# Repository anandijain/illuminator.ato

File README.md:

# illuminator
a device to capture timelapses of fluorescent petri dishes

[Onshape CAD](https://cad.onshape.com/documents/1effa1616a317fb48e7ffbf3/w/ae2fe78dc753e01a133967d8/e/a3ef25508ab919a74d42227d?renderMode=0&uiState=692bc1250b43d9fa593e8de2)

[YouTube](https://youtube.com/playlist?list=PL79kqjVnD2ENzYDWSiDm63MTBGJOrp2XY&si=uE8JB_jzI9ln5rCQ)

petri dish illuminator for timelapses 
the functionality basically has an 
* mcu turn on a bunch of lights
* light goes thru a diffuser
* hit the petri (excite the fluorescent protein)
* into a filter 
* imaged via timelapse on a DSLR 

there are two modes to use the device
Common to both modes is using a GPIO pin to turn on a mosfet that turns on an LED grid. 

## Raspberry Pi Pico 
the first is using a raspberry pi pico, and the second is using a full fledged Pi. 
However, we still need to tell the camera to take a photo while the lights are on. 
The pico accomplishes this by using a GPIO pin to drive an optocoupler, which connects to the [MC-DC2](https://www.dslrbodies.com/cameras/general-nikon-camera-info/nikon-mc-dc2-connector-pin.html) port. 
Basically the opto provides a short between the Tip and the Sleeve, triggering a photo to be taken.

## Raspberry Pi 
Unfortunately, this method requires providing power for the board and the Pi separately (two power cables). 
Basically, a USB cable is connects the Pi to Nikon's semi-proprietary UC-E6 "USB" port. 
Then we use `gphoto2` to trigger the camera and download it to the Pi.

the design is as follows, a 5V 5A (5A is excessive, you probably dont need more than 2-3A) wall wart plugs to a barrel jack

the barrel jack tip will go to VBus of the USB port and the 36 resistor-led pairs (all parallel)

the ground of the barrel goes to the gnd of the USB. 

The usb is an TYPE-A connector that is used solely for powering the Pico (DO NOT USE FOR A FULL PI, the USB 2.0 spec is limited at 1.5A but a Pi can draw 5A.)

## pinouts 
There is a TRS (i dont like JST) port used for connecting GPIO from Pi/Pico to the board.
The Tip of `trs_sig` is only used by the pico, and is for turning on the optocoupler
The Ring is used by both for turning on the FET (the LEDs)
The Sleeve is GND. 

Note: on the TRS breakout cable, white is tip (pico w pin GP16), red is ring (pico w pin GP17), black is sleeve (pico w pin 23 (GND))

A second TRS connector is used to connect the MC-DC2 connector from camera to the optocoupler. Unfortunately, it seems common that MC-DC2 uses a 2.5mm TRS, but I am just going to use an adapter so that I don't need to buy 2.5mm jacks that I'll never use. 

The path is 5v -> (R -> LED)* -> FET_DRAIN -> FET_SOURCE -> GND.

## camera 
* make sure no autofocus is on cuz that increases the time to shorting the MC-DC2 to an unknown amount of time

## lcd
* to get mc_dc2_test/lcd.py to work you need to copy [this](https://github.com/russhughes/st7789py_mpy/blob/master/lib/st7789py.py) to /lib/ with `mpremote`

remember to also copy the fonts 

the interface of the lcd is three buttons, two are for incrementing and decrementing the timelapse parameters the third is for advancing to the next parameter

todo ui:
- see if its possible to start timelapse when both + and - are hit simultaneously or something

TODO before order:

Done:
* fix mounting holes position
* cad enclosure and box 
* order the diffuser and lens
*silkscreen art 

## board images (no kicad schematic see main.ato)

## some BOM items
* [light diffuser](https://www.amazon.com/dp/B0818HYY8G)
* [hot plate for SMD soldering](https://www.amazon.com/dp/B082H12PPT)

### 8/28/25 

the general design will be relatively agnostic to the excitation wavelength, 
allowing multiple different proteins to be timelapsed 

TODO:
- resistor sizing for each string of LEDs
- can i PWM my N-mosfet that controls the leds? 

https://chatgpt.com/share/68b0b650-5c54-8009-a0fc-7b128db387fa

even though the excitation peak of [A. Victoria's GFP gene](https://www.fpbase.org/protein/avgfp/) is at 395 nm (UVA range), 
there is evidence that photobleaching occurs and can inhibit cell growth.

that, in addition to the eyes/skin risk of penetrating UV, we will use the weaker excitation peak of 
475 nm 

there are two primary routes to acheiving timelapses, 

the first is using a Pico and a port on the D7100 called MC-DC2 

the second is using a full RPi with gphoto2, this allows the collection of the photos onto the Pi

after extensive reading: the grid of LEDs will be 12 strings of 3 LEDs, powered by a 12V rail

maybe instead of a buck since it seems sparse to find preset 5V bucks at 3A (enought to power Pi)
and the ones that are adjustable seem annoying to implement

if we are going with the Pico, then its a bit easier since it's not going to need 5V 3A.

math

datasheet of led -> radiative flux (mW) -> photons/sec

concentration of GFP + QY + photons/sec -> number of emitted photons/sec

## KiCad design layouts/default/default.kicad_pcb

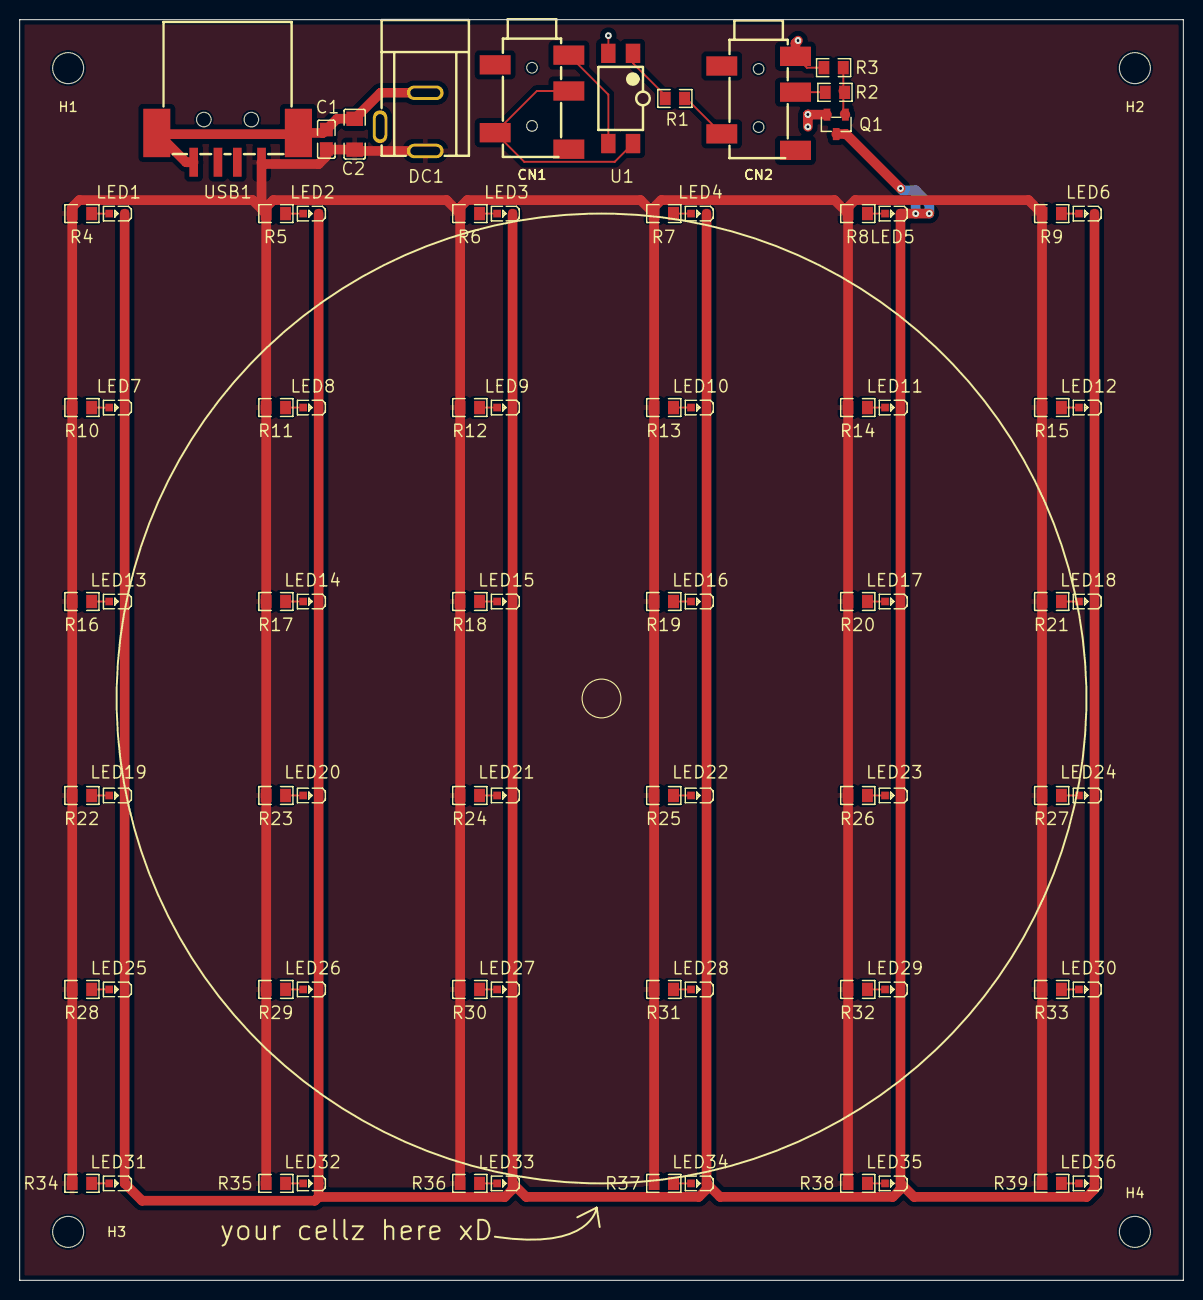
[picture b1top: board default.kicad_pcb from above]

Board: 2 copper layers, 120.0 x 130.0 mm, 87 parts (0 on the bottom side), 45 nets.

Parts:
C1: C0805
C2: C1206
CN1, CN2: AUDIO-SMD_PJ-327A5JJ
DC1: DC-IN-TH_DC-005-A200
H1, H2, H3, H4: MountingHole_3.2mm_M3
LED1, LED2, LED3, LED4, LED5, LED6, LED7, LED8, LED9, LED10, LED11, LED12, LED13, LED14, LED15, LED16, LED17, LED18, LED19, LED20, LED21, LED22, LED23, LED24, LED25, LED26, LED27, LED28, LED29, LED30, LED31, LED32, LED33, LED34, LED35, LED36: LED0603-RD_BLUE
Q1: SOT-23-3_L2.9-W1.3-P1.90-LS2.4-BR
R1, R2, R3, R4, R5, R6, R7, R8, R9, R10, R11, R12, R13, R14, R15, R16, R17, R18, R19, R20, R21, R22, R23, R24, R25, R26, R27, R28, R29, R30, R31, R32, R33, R34, R35, R36, R37, R38, R39: R0805
U1: SMD-4_L4.6-W6.5-P2.54-LS10.2-TL
USB1: USB-A-SMD_USB-234-BCW

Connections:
G: Q1.1, R2.2, R3.1
GND: C1.2, C2.2, CN2.1, DC1.2, Q1.2, R3.2, U1.2, USB1.4, USB1.5, USB1.6
K: LED1.1, LED2.1, LED3.1, LED4.1, LED5.1, LED6.1, LED7.1, LED8.1, LED9.1, LED10.1, LED11.1, LED12.1, LED13.1, LED14.1, LED15.1, LED16.1, LED17.1, LED18.1, LED19.1, LED20.1, LED21.1, LED22.1, LED23.1, LED24.1, LED25.1, LED26.1, LED27.1, LED28.1, LED29.1, LED30.1, LED31.1, LED32.1, LED33.1, LED34.1, LED35.1, LED36.1, Q1.3
S: CN1.1, U1.3
T: CN2.4, R1.1
VCC: C1.1, C2.1, DC1.1, R4.1, R5.1, R6.1, R7.1, R8.1, R9.1, R10.1, R11.1, R12.1, R13.1, R14.1, R15.1, R16.1, R17.1, R18.1, R19.1, R20.1, R21.1, R22.1, R23.1, R24.1, R25.1, R26.1, R27.1, R28.1, R29.1, R30.1, R31.1, R32.1, R33.1, R34.1, R35.1, R36.1, R37.1, R38.1, R39.1, USB1.1
_1: R1.2, U1.1
footprint-A-0: LED1.2, R4.2
footprint-A-1: LED11.2, R14.2
footprint-A-2: LED12.2, R15.2
footprint-A-3: LED13.2, R16.2
footprint-A-4: LED14.2, R17.2
footprint-A-5: LED15.2, R18.2
footprint-A-6: LED16.2, R19.2
footprint-A-7: LED17.2, R20.2
footprint-A-8: LED18.2, R21.2
footprint-A-9: LED19.2, R22.2
footprint-A-10: LED20.2, R23.2
footprint-A-11: LED2.2, R5.2
footprint-A-12: LED21.2, R24.2
footprint-A-13: LED22.2, R25.2
footprint-A-14: LED23.2, R26.2
footprint-A-15: LED24.2, R27.2
footprint-A-16: LED25.2, R28.2
footprint-A-17: LED26.2, R29.2
footprint-A-18: LED27.2, R30.2
footprint-A-19: LED28.2, R31.2
footprint-A-20: LED29.2, R32.2
footprint-A-21: LED30.2, R33.2
footprint-A-22: LED3.2, R6.2
footprint-A-23: LED31.2, R34.2
footprint-A-24: LED32.2, R35.2
footprint-A-25: LED33.2, R36.2
footprint-A-26: LED34.2, R37.2
footprint-A-27: LED35.2, R38.2
footprint-A-28: LED36.2, R39.2
footprint-A-29: LED4.2, R7.2
footprint-A-30: LED5.2, R8.2
footprint-A-31: LED6.2, R9.2
footprint-A-32: LED7.2, R10.2
footprint-A-33: LED8.2, R11.2
footprint-A-34: LED9.2, R12.2
footprint-A-35: LED10.2, R13.2
footprint-R-0: CN1.3, CN1.4, U1.4
footprint-R-1: CN2.3, R2.1

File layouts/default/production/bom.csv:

Designator,Footprint,Quantity,Value,LCSC Part #
C1,C0805,1,,C49678
C2,C1206,1,,C15008
"CN1, CN2",AUDIO-SMD_PJ-327A5JJ,2,,C668605
DC1,DC-IN-TH_DC-005-A200,1,,C720557
"LED1, LED10, LED11, LED12, LED13, LED14, LED15, LED16, LED17, LED18, LED19, LED2, LED20, LED21, LED22, LED23, LED24, LED25, LED26, LED27, LED28, LED29, LED3, LED30, LED31, LED32, LED33, LED34, LED35, LED36, LED4, LED5, LED6, LED7, LED8, LED9",LED0603-RD_BLUE,36,,C965807
Q1,SOT-23-3_L2.9-W1.3-P1.90-LS2.4-BR,1,,C347475
R1,R0805,1,,C95781
"R10, R11, R12, R13, R14, R15, R16, R17, R18, R19, R20, R21, R22, R23, R24, R25, R26, R27, R28, R29, R30, R31, R32, R33, R34, R35, R36, R37, R38, R39, R4, R5, R6, R7, R8, R9",R0805,36,,C114245
R2,R0805,1,,C105577
R3,R0805,1,,C2907217
U1,SMD-4_L4.6-W6.5-P2.54-LS10.2-TL,1,,C66405
USB1,USB-A-SMD_USB-234-BCW,1,,C720528

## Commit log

2025-08-29 a bunch of notes
2025-08-29 nearing v1
2025-08-29 documentation
2025-08-29 decoupling caps
2025-08-29 dont even know whats up w the max current thing
2025-08-30 vibe coded garbage to try to get the pcb to not have duplicate refdes
    at least a rough draft of the pcb is done tho
    the current workflow is
    delete everything on pcb, save, ato build, uv run old.py, open kicad, then manually delete the extras, and move the remaining refdes and layout route as normal.
2025-08-30 gerbers, mounting holes, gnd and vcc fills
2025-08-30 found important bug in headphone jack pinout. commiting before ato build
2025-08-30 besides mounting holes, the pcb is almost there
2025-08-30 just manually do mounting holes since the people at atopile are LYING to me
2025-08-30 done
2025-08-30 gerbers
2025-08-30 silkscreen bug
2025-08-30 step files
2025-08-31 how could i forget the silkscreen art??
2025-08-31 finish todoes
2025-08-31 the camera only takes pictures if BOTH the Ring and Tip are shorted to ground. so we add a connection on board from R ~ T
    have not changed layout/routing yet
2025-08-31 add the T ~ R trace, redo the fill zone and rebuild the gerbers
2025-08-31 address some DFM warnings and errors
    supposedly i fixed these:
    * soldermask opening exposing trace (1)
    * at least some of the "silkscreen to pad" errors
    * silkscreen to hole
    * annular ring warnings, changed via diam to .7 ( should also improve thermals a bit)
2025-08-31 fix a dfm error about placing a via directly under a pad (lead to hole distance)
2025-08-31 idek if i changed anything lol
2025-08-31 unignore the bom + pos. reexport step file
2025-09-17 ibom
2025-09-19 notes and pcb test code
2025-09-19 screen test works and untested timelapse code written for the pcb_test
2025-09-19 intermediate no scene redraw
2025-09-19 rudimentary but no start mechanism
2025-09-19 all together now
2025-09-27 some improvements
2025-10-12 rename to src
2025-10-20 rename the main code and add a real finalized pinout
2025-11-30 add links in readme
2026-01-07 add images
2026-01-07 add link to diffuser
2026-01-07 hot plate in bom
2026-04-09 pictures and links
